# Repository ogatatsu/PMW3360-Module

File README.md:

# PMW3360-Module

## 部品

| Name | Qty | Description | Manufacturer
----|----|----|----
| U1 | 1 | PMW3360-T2QU | PixArt Imaging Inc. |
| U2 | 1 | 1.9V VOLTAGE REGULATOR, S-1313D19-M5T1U3 | ABLIC Inc. |
| C1 | 1 | Capacitor, 4.7uF, 1608 |  |
| C2,C4,C5 | 3 | Capacitor, 0.1uF, 1608 |  |
| C3,C6 | 2 | Capacitor, 10uF, 1608 |  |
| R1 | 1 | Resistor, 39 Ohm, 1608 ||
| R2 | 1 | Resistor, 10k Ohm, 1608 ||
## License

https://creativecommons.org/licenses/by/4.0/

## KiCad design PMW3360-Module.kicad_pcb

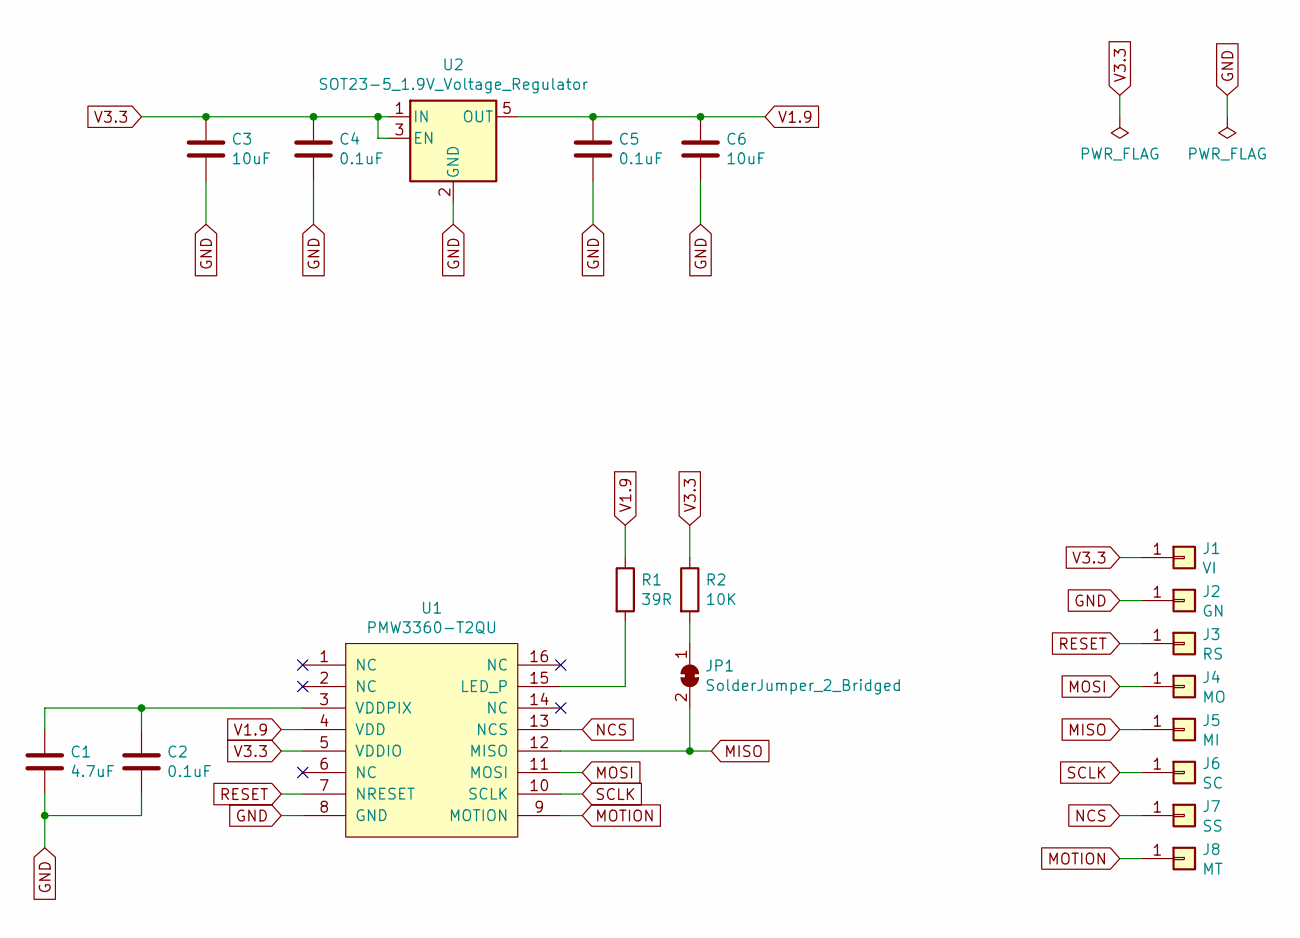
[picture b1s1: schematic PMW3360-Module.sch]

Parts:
C1: 4.7uF; 1608
C2, C4, C5: 0.1uF; 1608
C3, C6: 10uF; 1608
J1: VI; Wirepad
J2: GN; Wirepad
J3: RS; Wirepad
J4: MO; Wirepad
J5: MI; Wirepad
J6: SC; Wirepad
J7: SS; Wirepad
J8: MT; Wirepad
JP1: SolderJumper_2_Bridged; SolderJumper-2_P1.3mm_Bridged_Pad1.0x1.5mm
R1: 39R; 1608
R2: 10K; 1608
U1: PMW3360-T2QU
U2: SOT23-5_1.9V_Voltage_Regulator; SOT-23-5

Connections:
GND: C1.2, C2.2, C3.2, C4.2, C5.2, C6.2, J2.1, U1.8 (GND), U2.2 (GND)
MISO: J5.1, JP1.2 (B), U1.12 (MISO)
MOSI: J4.1, U1.11 (MOSI)
MOTION: J8.1, U1.9 (MOTION)
NCS: J7.1, U1.13 (NCS)
unnamed: C1.1, C2.1, U1.3 (VDDPIX)
unnamed: JP1.1 (A), R2.2
unnamed: R1.2, U1.15 (LED_P)
RESET: J3.1, U1.7 (NRESET)
SCLK: J6.1, U1.10 (SCLK)
V1.9: C5.1, C6.1, R1.1, U1.4 (VDD), U2.5 (OUT)
V3.3: C3.1, C4.1, J1.1, R2.1, U1.5 (VDDIO), U2.1 (IN), U2.3 (EN)

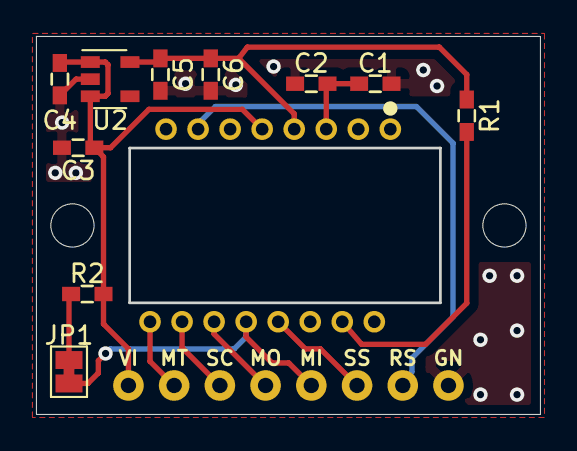
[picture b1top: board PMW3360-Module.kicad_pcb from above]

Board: 2 copper layers, 28.0 x 21.0 mm, 21 parts (0 on the bottom side), 12 nets.

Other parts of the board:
hole1, hole2: hole_2.4mm

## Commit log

2019-05-03 add schematic
2019-05-03 add image
